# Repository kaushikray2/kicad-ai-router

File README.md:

# KiCad AI Router

Developed by [SiliconBrane Inc](https://www.siliconbrane.com)

KiCad AI Router is a routing and routing-repair system for KiCad 10.

The project started from a simple observation after a lot of experiments: large language models are terrible at geometry, but surprisingly useful for deciding what to try next.

Instead of letting an AI draw copper directly, KiCad AI Router uses deterministic routing tools that generate all board geometry. The AI, when enabled, only chooses strategies and tool ordering. Every change is verified before it is accepted.

If a routing step introduces new violations, it gets reverted.

The goal is not to replace PCB designers or compete with professional routing workflows. The goal is to automate as much of the repetitive routing work as possible while producing results that survive real KiCad verification.

---

## How it works

The system is built around a simple rule:

> The router decides. The gate judges.

Routing tools generate candidate changes. Those changes are then checked using:

- `kicad-cli` DRC
- Exact clearance validation
- Per-layer track accounting
- Connectivity checks
- Split-net analysis

A change is considered successful only if the gate accepts it.

Not because an LLM says it looks good.
Not because connectivity improved.
Not because a heuristic thinks it is better.

Only the gate's result matters.

---

## What it can do

### Multi-engine portfolio and full-board passes

Full-board routing runs in `AUTO` mode (the default, measured path):

- **Engine portfolio (`engine_portfolio`):** Before standard passes, candidate routes from stripped base can run across TraceMaker variants (`tm_relax` enabled by default; `tm_global`, `tm_escape` opt-in) as well as bundled **Freerouting 2.5** and **KiCadRoutingTools (KRT)** in the Docker backend. Candidates are judged faults-first by the gate so high-violation routes never win on connectivity alone.
- **Layer law and graded layer pricing (`no_tracks_on`, `layer_cost`, `layer_law_policy`):** Inner reference/power planes can be hard-banned (`no_tracks_on`), automatically escalated from plane-protected to open when signal nets stay split (`layer_law_policy=auto`), or priced per cell (`layer_cost`, e.g. `In1.Cu=10,In2.Cu=10`) so inner layers are used only when outer detours are worse.
- **Iterative triage passes:** Up to `max_passes` TraceMaker passes promote failing signal nets (or priority pairs/corridors) and retain the best pass on connectivity, split count, DRC faults, and cost-weighted wirelength.

### Post-pass routing repair

When full-board passes leave split nets or isolated pour islands, deterministic repair stages run in sequence:

- **Local and board-scale finishing (`finish_leg`, `long_finish`, `ilp_repair`):** 3D grid A* finishing (respecting configured bans and layer costs), single- and cut-set victim displacement with re-bridging, and large-window hard-A* paths for distant fragments.
- **Pour stitching and plane healing (`stitch`, `heal`, `prune`):** Via stitching and short track bridges for floating pour pads, additive bridges (with island via-hunting) for split power/ground planes, dead-copper pruning, and a post-prune pour pass.
- **Windowed engine re-route (`reroute_window`, opt-in):** Locks copper outside a stuck connection's corridor (preserving user-locked tracks by UUID), lets TraceMaker `--reroute` rip and re-route the window, and accepts the trade under a configurable key (`connectivity` or `faults`).

Finisher, stitch, and heal additions are checked before commit against exact clearance, keepout, drill (`hole_clearance` / `hole_to_hole`), and `Edge.Cuts` geometry, and every pipeline step is gated by `kicad-cli` DRC plus the banned-layer track census (reverting steps that degrade the stage's acceptance key).

### AUTO mode vs. LLM mode

- **AUTO mode (default):** Deterministic strategy and repair sequence, no LLM required. All published benchmarks and backend self-tests run in `AUTO` mode.
- **LLM mode (experimental):** Any OpenAI-compatible endpoint drives the `v1.8` tool loop (`route`, `gate`, `finish_leg`, `long_finish`, `ilp_repair`, `stitch_gnd`, `heal`, `prune`) without emitting geometry. Newer `v1.9+` stages (`portfolio`, `reroute_window`, `layer_law_policy`) run in `AUTO` mode only; on endpoint error, `LLM` mode falls back to `AUTO`.

### Automated tests and self-tests

- Unit and pcbnew fixture tests in `tests/`, run in GitHub Actions CI inside the KiCad 10 backend image on every push (skipping `pcbnew`-dependent fixtures cleanly outside KiCad).
- Built-in end-to-end backend self-tests (`docker/selftest/`, triggered via the web UI or `POST /api/selftest/run`).

---

## Results

All measurements below were run in deterministic `AUTO` mode (`strip_existing=true`) and verified with `kicad-cli` DRC plus the pipeline's connectivity and banned-layer census.

### Early PCBench sample (`v1.6`–`v1.7`, pre-portfolio baseline)

- 24-board development sample drawn from the 59-board PCBench corpus (`AUTO` mode, default `In1.Cu` ban): **23 of 24** boards routed to 0 unconnected items, with 1 router-added copper-clearance violation across the 23 completed boards.

### `dataset-v3` corpus (`v1.8`, layer-law ablation)

- **139** public KiCad boards (`dataset-v3/` manifests and submission drivers committed in-repo; **432** backend runs across policy arms).
- On completed boards: median wirelength **0.83×** the original human-routed board; via count typically **1.0×–1.1×**.
- Key finding: net-ordering heuristics (`first_nets_policy`, `pass_advice`) had negligible effect, whereas layer-law selection (`layer_law_policy=auto`, Variant B-first with Variant A escalation on ≥4-layer pour boards) closed most of the 44-connection single-policy vs. oracle gap on the 54 multilayer boards.

### Tiered benchmark & `P2.0` fault census (`v1.9.5`–`v1.9.6`)

- Decomposing **60** production run ledgers at three gates (`base` → `routed` → `final`) showed **0 net router-added copper DRC violations** on completed bench boards — the raw copper violations (416 across 43 boards, led by `solder_mask_bridge` and `copper_edge_clearance`) were already present in the unrouted input placements.
- Scored against each board's own stripped input (`CP_delta`: 0 unconnected, 0 splits, and no increase in DRC faults over base), completion stands at **1.00 (easy)**, **1.00 (medium)**, and **0.90 (hard)**. *(The standalone tier-sweep harness with hash-cached prepared inputs is tracked for commit under `#62`.)*

### Known limitation

Congestion remains the hardest problem.

Several approaches were tested, including:

- ILP candidate selection
- Improved victim re-bridging
- Attempt ranking
- PathFinder-style negotiation routing

None showed measurable improvement on the remaining congestion-bound failures.

The project is a strong routing finisher and routing-repair system.

It is not a magic autorouter.

---

## Requirements

### Required

- KiCad 10
- Python 3
- `kicad-cli`

### For full-board routing

- TraceMaker 0.12.1

Place the binary in:

```
tracemaker/0.12.1/
```

inside the backend data directory.

The backend fetches TraceMaker from the configured URL (`TRACEMAKER_URL` or the `tracemaker.url` config) -- on first startup and via its update endpoint -- and installs it only after a sha256 check against the recorded hash for that version (first use of a new version is trust-on-first-use). A local file path or `file://` URL can be configured instead of a download.

### For AI mode

Any OpenAI-compatible API endpoint.

AUTO mode does not require an LLM.

### Backend

Either:

- Docker (recommended)
- A host machine with KiCad 10 and Python 3 capable of running `docker/server.py`

---

## Installation

### Installing the KiCad plugin

Add the repository to KiCad's Plugin and Content Manager
(Preferences -> Plugin and Content Manager -> Manage Repositories)
by URL:

```
https://raw.githubusercontent.com/kaushikray2/kicad-ai-router/main/pcm-repo/repository.json
```

or download the package zip from this repository and install it
from the Plugin and Content Manager via "Install from File...":

```
pcm-repo/ai-router-1.12.5.zip
```

Configure the backend connection in:

```
~/.config/ai_router/config.json
```

#### Windows notes

- The PCM installs the package under your **Documents** folder:
  `Documents\KiCad\10.0\3rdparty\plugins\ca_siliconbrane_ai-router\`
  (the package folder is the package identifier with dots replaced
  by underscores).
- After installing or updating, **fully restart KiCad** -- the
  toolbar button and the Tools -> External Plugins entry appear
  only once the PCB Editor has restarted and re-scanned its
  plugins.
- Button still missing? Open the Python Console
  (Tools -> Scripting Console) in the PCB Editor and run
  `import ai_router`. If registration failed, the console shows
  `ai_router: plugin not registered (...)` -- the text in
  brackets names the module that failed to load.
- The configuration file on Windows is
  `%USERPROFILE%\.config\ai_router\config.json`.
- **v1.11.5 and earlier:** the PCM package was built without the
  entry point KiCad's plugin loader looks for, so a PCM install
  was never discovered (fixed in v1.11.6 -- update if you can).
  If you are stuck on 1.11.5, copy the `ai_router` folder from
  the installed package (path above) into
  `Documents\KiCad\10.0\scripting\plugins\ai_router\` and
  restart KiCad; remove that copy once you update past 1.11.5.

---

### Starting the backend

```bash
cd docker
docker build -f Dockerfile -t ai-router-backend ..
docker run -d -p 127.0.0.1:8731:8731 -v $PWD/data:/data ai-router-backend
```

On first startup the backend creates:

- Configuration files
- Authentication token
- Runtime directories

The backend also includes built-in self-tests using public sample boards.

Tests can be run through:

- The status page
- `POST /api/selftest/run`

#### Time limits and best-so-far results

Backend routing runs are not all-or-nothing. While a job runs,
the result artifact (`result.kicad_pcb` in the job's run
directory, served at `GET /api/runs/<id>/result`) is rewritten
whenever a finished pass or portfolio variant beats the best
gate key seen so far, and every write is atomic (written beside
the target, then renamed over it), so the file is always a
complete, gate-checkable board. Killing a job, cancelling it,
or losing the runner at any point leaves the best routing found
so far as the artifact instead of nothing.

A run can also be time-boxed with the routing setting
`time_limit_s` (seconds, `0` = no limit -- the default; settable
in the backend's `config.json` routing section, via
`POST /api/config`, or as a per-job override). At job start the
limit is converted once into a single absolute deadline -- one
point in time, shared by every worker in the run (the pipeline,
its worker subprocesses and the portfolio race legs all compare
against the same instant). When the deadline passes, no new
work starts: the run finishes with the best board so far. A
result the deadline actually truncated is labelled in the job
status (`deadline_hit` / `nondeterministic`) -- how much routing
got done by then depends on machine speed. A deadline that
never binds changes nothing and labels nothing, and
deadline-free runs keep the usual determinism contract.

---

## Repository layout

```text
ai_router/
├── worker.py
├── pipeline.py
├── orchestrator.py

docker/
├── server.py
├── run_job.py
├── selftest/

dataset-v1/
dataset-v2/
dataset-v3/

CHANGELOG.md
```

### Important files

**worker.py**

Contains the geometry tools that execute under KiCad's Python environment.

**pipeline.py**

Wraps routing and repair tools with gate validation.

**orchestrator.py**

Implements AUTO mode and LLM-assisted strategy selection.

**dataset-v1 / v2 / v3**

Benchmark datasets, runners and result archives used during development.

**CHANGELOG.md**

The full engineering history of the project, including failed experiments, discarded ideas and the data that led to design decisions.

---

## Philosophy

Most AI routing projects start by asking:

> Can an LLM route a PCB?

This project asks a different question:

> Can a deterministic router become better if an LLM only decides what to try next?

Everything in this repository follows that idea.

The AI is optional.

The geometry is deterministic.

Verification is mandatory.

---

## Appendix: design notes from the development record

*(Moved verbatim from CHANGELOG.md on 2026-11-25, #149 D10 -- the changelog keeps versions and dated records only.)*

Routes a board from inside KiCad using the measured hybrid procedure:
an LLM (any OpenAI-compatible endpoint) makes **strategy** decisions only,
while deterministic tools do all geometry — TraceMaker for full-board
passes, a scripted grid-A* finisher for stuck legs, a connectivity-probe
stitcher for GND pour islands, and `kicad-cli` DRC as the only gate.

This is the pipeline validated by hand on the in-house board (Rev K → K2 → K3
→ in-place finish: 0 unconnected), packaged as a plugin. The LLM never
emits coordinates or traces; every effective experiment showed that path
is a dead end, and every fix moved the design back toward this split.

## Install

Copy the `ai_router/` folder into KiCad's scripting plugins directory:

    ~/.local/share/kicad/10.0/scripting/plugins/ai_router/

Restart KiCad (or refresh external plugins). The plugin appears as
**AI Router (LLM orchestrator)** with a toolbar button.

## Use

1. Open the board in Pcbnew, save it, launch the plugin.
2. Configure: endpoint, model, API key (if the endpoint needs one),
   TraceMaker binary path, mode, max passes, banned layers.
   Defaults point at the home large backend host llama.cpp server
   (`http://backend host:8080/v1`, `qwen3-coder-30b`).
3. Run. The plugin works on **copies** in an `ai-route-<timestamp>/`
   folder next to your board — your open board is never modified.
   A `ledger.json` in that folder records every step.
4. When it finishes, "Open result board" loads `final.kicad_pcb`.

## Modes

- **llm** — the model drives the tool loop under a written playbook
  (orient → route with protected first-nets → gate → promote casualties →
  finish stuck legs in place → stitch pour islands → done). If the
  endpoint errors, the run falls back to AUTO for the remainder.
- **auto** — the same playbook as deterministic rules, no model needed.

Endpoints without native tool calling are handled by a JSON-action
fallback parser (the model answers with `{"tool": ..., "args": ...}`).

## Tools the orchestrator can call

| tool | what it does |
|---|---|
| `board_summary` | nets, pad counts, split nets via KiCad connectivity |
| `scorecard` | worst decoupling caps by distance to nearest same-net pad |
| `route` | one TraceMaker pass (layer law enforced by `--no-tracks-on`) |
| `gate` | `kicad-cli pcb drc --refill-zones`; unconnected decomposed into pour vs signal |
| `finish_leg` | grid-A* finisher for one net; single-net displacement + re-bridge when blocked; planner clearance = board rule + margin |
| `stitch_gnd` | probes every GND pad's connectivity cluster; one stitch via per floating island, verified by re-probe |
| `done` | end the run |

## Rules baked in (measured, not guessed)

- **Refill before every save.** Zone fills are stored polygons; any layout
  change leaves them stale and the GUI shows pours flowing over new
  traces. Strip, every route pass, and finalize all refill first.
- **Layer law by construction:** In1.Cu (GND plane) is never routed;
  In2.Cu (power plane) banned by default (configurable).
- **First-net protection does not bind between first nets** — a protected
  net can still be ripped by another protected net; that is what
  `finish_leg` exists for.
- **Pour items ≠ signal failures.** Judge a pass by split signal nets;
  pour fragmentation is closed at the end by stitching.
- The gate (KiCad DRC after refill) is the only verdict — never the
  router's own counts.

## Honest limits

- TraceMaker is a heuristic search: identical inputs vary run to run
  (measured 5–9 unconnected across equivalent passes). The triage loop +
  finisher absorb that variance; a single pass guarantees nothing.
- A 30B local model's judgment is the weak link. The deterministic tools
  carry correctness; AUTO mode is the safety net and the baseline.
- `finish_leg` handles one missing leg of one net per call and displaces
  at most one net. Boards needing multi-net surgery still need a human.

## License

GPL-3.0-or-later.

Copyright (c) 2026 SiliconBrane Inc.

The sample boards included in `docker/selftest/` are public open-hardware designs and remain covered by their respective licenses.

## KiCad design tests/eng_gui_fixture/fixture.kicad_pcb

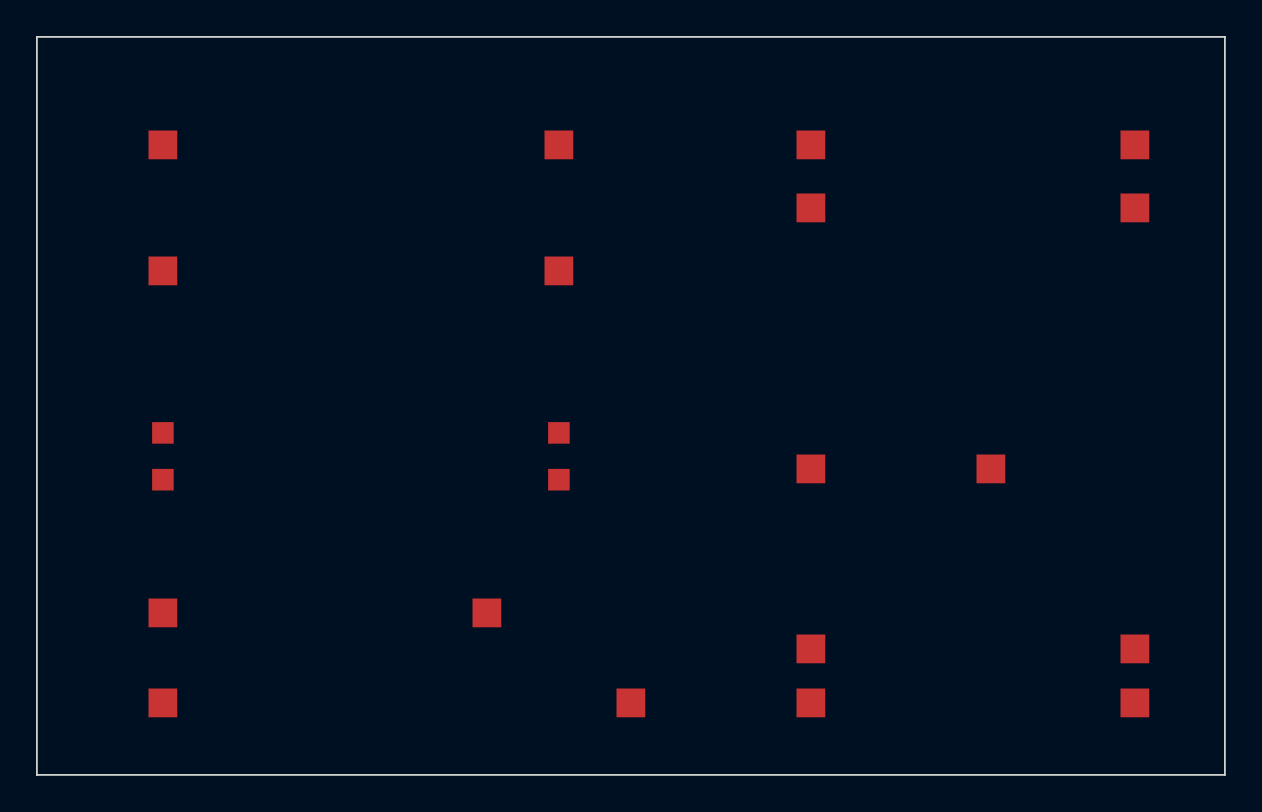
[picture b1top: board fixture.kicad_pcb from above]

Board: 2 copper layers, 66.0 x 41.0 mm, 18 parts (0 on the bottom side), 11 nets, no tracks yet.

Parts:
U1, U2, U3, U4, U5, U6, U7, U8, U9, U10, U11, U12, U13, U14, U15, U16, U17, U18: FIXTURE

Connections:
CLK_N: U5.2, U6.2
CLK_P: U5.1, U6.1
GND: U17.2, U18.2
HV_A: U11.1, U12.1
HV_B: U13.1, U14.1
LEN_A: U7.1, U8.1
LEN_B: U9.1, U10.1
QUIET_X: U15.1, U16.1
RF_FAIL: U3.1, U4.1
RF_IN: U1.1, U2.1
VCC5: U17.1, U18.1

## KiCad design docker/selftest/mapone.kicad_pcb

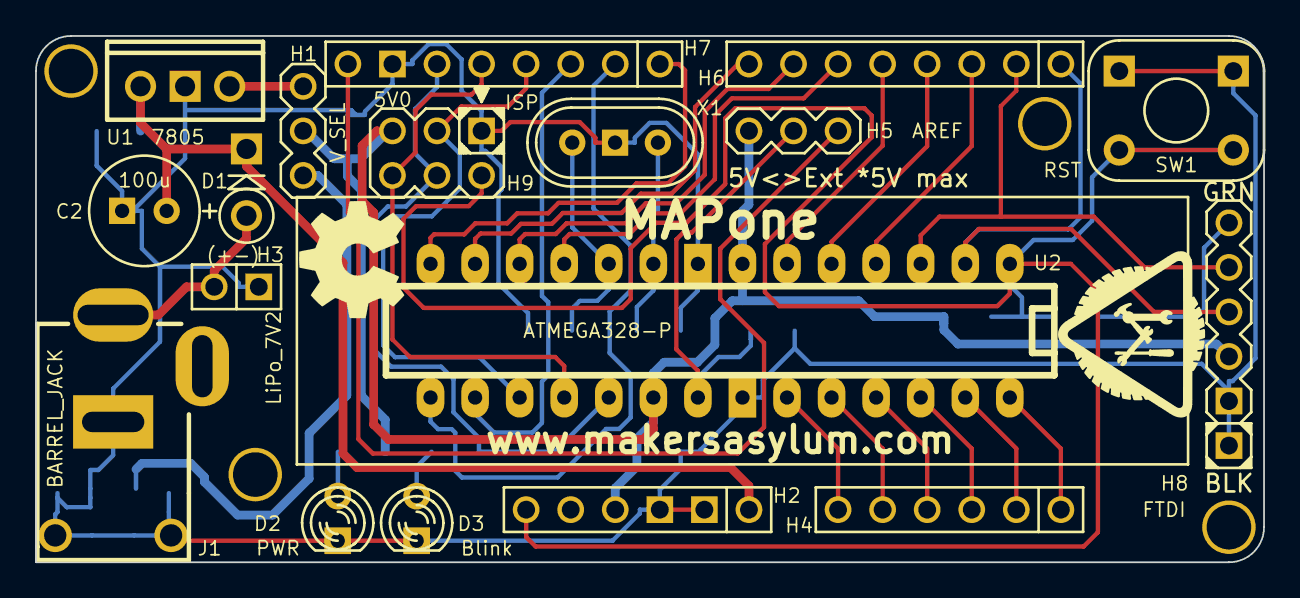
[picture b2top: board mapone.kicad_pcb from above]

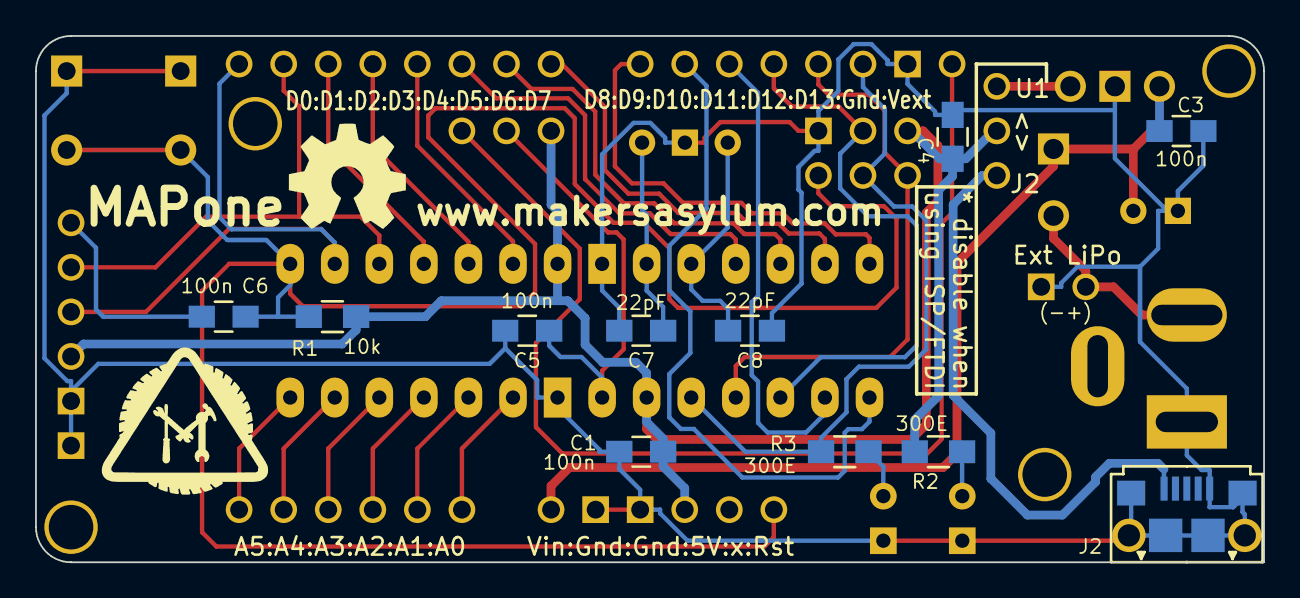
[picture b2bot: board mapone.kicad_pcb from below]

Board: 2 copper layers, 70.0 x 30.0 mm, 37 parts (13 on the bottom side), 34 nets.

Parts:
C1, C3, C4, C5, C6: 100n; C_0805_HandSoldering
C2: 100u; Elko_vert_11.2x6.3mm_RM2.5
C7, C8: 22pF; C_0805_HandSoldering
D1: 1N4007; Diode_DO-41_SOD81_Vertical_KathodeUp
D2: PWR; LED-3MM
D3: Blink; LED-3MM
H1: V_SEL; Header_3
H2: Power; Socket_Strip_Straight_1x06
H3: LiPo_7V2; Pin_Header_Straight_1x02
H4: ANALOG; Socket_Strip_Straight_1x06
H5: AREF; Header_A_REF
H6: IO_L; Socket_Strip_Straight_1x08
H7: IO_H; Socket_Strip_Straight_1x08
H8: FTDI; Header_FTDI
H9: ISP; Header_ICSP
J1: BARREL_JACK; JACK_ALIM
J2: USB-Micro; USB_B_Micro
P1, P2, P3, P4: CONN_1; vite_3mm
R1: 10k; R_0805_HandSoldering
R2, R3: 300E; R_0805_HandSoldering
SW1: RST; SW-PB
U1: 7805; LM78XXV
U2: ATMEGA328-P; DIP-28__300_ELL_ZIF
X1: 16MHz; Crystal_HC49-U_Vertical_3Pin
Z1, Z2: CONN_1; MA_Logo2
Z6, Z7: CONN_1; OSHW_6mm

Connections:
/5V: C1.1, C4.1, H1.2, H2.4, H5.1, H8.3, H9.2, R1.1, R2.2, U2.7, U2.20
/AD0: H4.6, U2.23
/AD1: H4.5, U2.24
/AD2: H4.4, U2.25
/AD3: H4.3, U2.26
/AD4_SDA: H4.2, U2.27
/AD5_SCL: H4.1, U2.28
/AREF: C5.1, H5.2, U2.21
/MISO: H7.5, H9.1, U2.18
/MOSI_P: H7.4, H9.4, U2.17
/PB0: H7.1, U2.14
/PB1_P: H7.2, U2.15
/PD2: H6.3, U2.4
/PD3_P: H6.4, U2.5
/PD4: H6.5, U2.6
/PD5_P: H6.6, U2.11
/PD6_P: H6.7, U2.12
/PD7: H6.8, U2.13
/RST: C6.1, H2.6, H9.5, R1.2, SW1.2, U2.1
/RXD: H6.1, H8.4, U2.2
/SCK: H7.6, H9.3, R3.1, U2.19
/SS_P: H7.3, U2.16
/TXD: H6.2, H8.5, U2.3
/V_IN: C2.1, C3.2, D1.2, H2.1, U1.VI
/V_REG: H1.1, U1.VO
/V_USB: H1.3, J2.1
/Vext: H5.3, H7.8
GND: C1.2, C2.2, C3.1, C4.2, C5.2, C7.2, C8.2, D2.2, D3.2, H2.2, H2.3, H3.1, H7.7, H8.1, H8.2, H9.6, J1.2, J2.5, J2.T1, J2.T2, J2.T3, J2.T4, J2.T5, J2.T6, SW1.1, U1.GND, U2.8, U2.22, X1.3
unnamed: C6.2, H8.6
unnamed: C7.1, U2.9, X1.1
unnamed: C8.1, U2.10, X1.2
unnamed: D1.1, H3.2, J1.1
unnamed: D2.1, R2.1
unnamed: D3.1, R3.2

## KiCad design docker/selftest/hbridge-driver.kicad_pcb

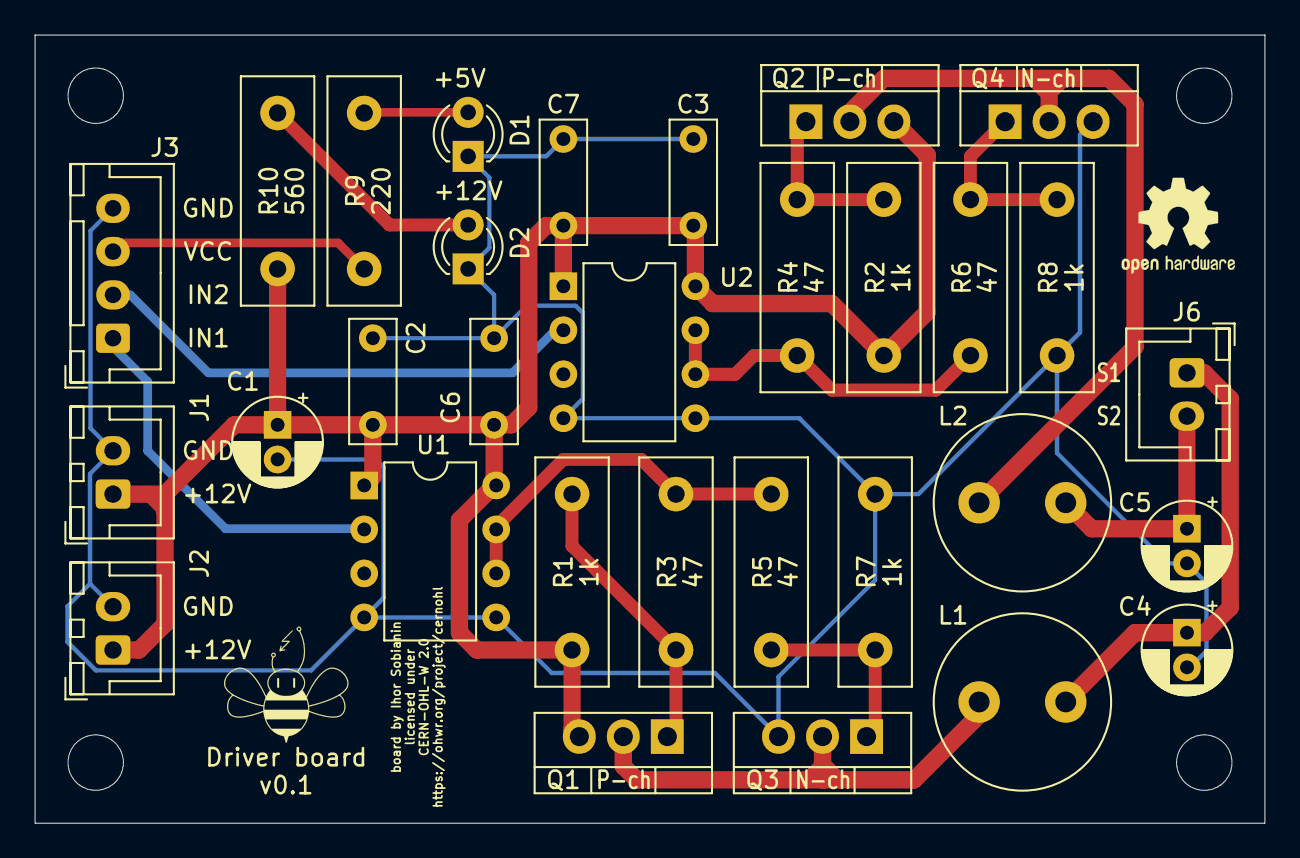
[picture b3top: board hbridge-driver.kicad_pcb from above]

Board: 2 copper layers, 71.0 x 45.5 mm, 31 parts (0 on the bottom side), 17 nets.

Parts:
C1, C4, C5: 22u; CP_Radial_D5.0mm_P2.00mm
C2, C3, C6, C7: 100nF; C_Disc_D7.0mm_W2.5mm_P5.00mm
D1, D2: LED; LED_D3.0mm
J1, J2, J6: Conn_01x02; JST_XH_B2B-XH-A_1x02_P2.50mm_Vertical
J3: Conn_01x04; JST_XH_B4B-XH-A_1x04_P2.50mm_Vertical
L1, L2: 33u; L_Radial_D10.0mm_P5.00mm_Neosid_SD12_style3
Q1, Q2: IRF9Z34NPBF; TO-220-3_Vertical
Q3, Q4: IRFZ24NPBF; TO-220-3_Vertical
R1, R2, R7, R8: 1k; R_Box_L13.0mm_W4.0mm_P9.00mm
R3, R4, R5, R6: 47; R_Box_L13.0mm_W4.0mm_P9.00mm
R9: 220; R_Box_L13.0mm_W4.0mm_P9.00mm
R10: 560; R_Box_L13.0mm_W4.0mm_P9.00mm
U1, U2: TC4420CPA; DIP-8_W7.62mm

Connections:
+5V: J3.3, R9.1
+12V: C1.1, C2.1, C3.1, C6.1, C7.1, J1.1, J2.1, Q1.3, Q2.3, R1.2, R2.2, R10.1, U1.1, U1.8, U2.1, U2.8
GND: C1.2, C2.2, C3.2, C4.2, C5.2, C6.2, C7.2, D1.1, D2.1, J1.2, J2.2, J3.4, Q3.3, Q4.3, R7.1, R8.1, U1.4, U1.5, U2.4, U2.5
IN1: J3.1, U1.2
IN2: J3.2, U2.2
unnamed: C4.1, J6.1, L1.2
unnamed: C5.1, J6.2, L2.2
unnamed: D1.2, R9.2
unnamed: D2.2, R10.2
unnamed: L1.1, Q1.2, Q3.2
unnamed: L2.1, Q2.2, Q4.2
unnamed: Q1.1, R1.1, R3.2
unnamed: Q2.1, R2.1, R4.2
unnamed: Q3.1, R5.2, R7.2
unnamed: Q4.1, R6.2, R8.2
unnamed: R3.1, R5.1, U1.6, U1.7
unnamed: R4.1, R6.1, U2.6, U2.7

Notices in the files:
docker/selftest/hbridge-driver.kicad_pcb:
licensed under
CERN-OHL-W 2.0
